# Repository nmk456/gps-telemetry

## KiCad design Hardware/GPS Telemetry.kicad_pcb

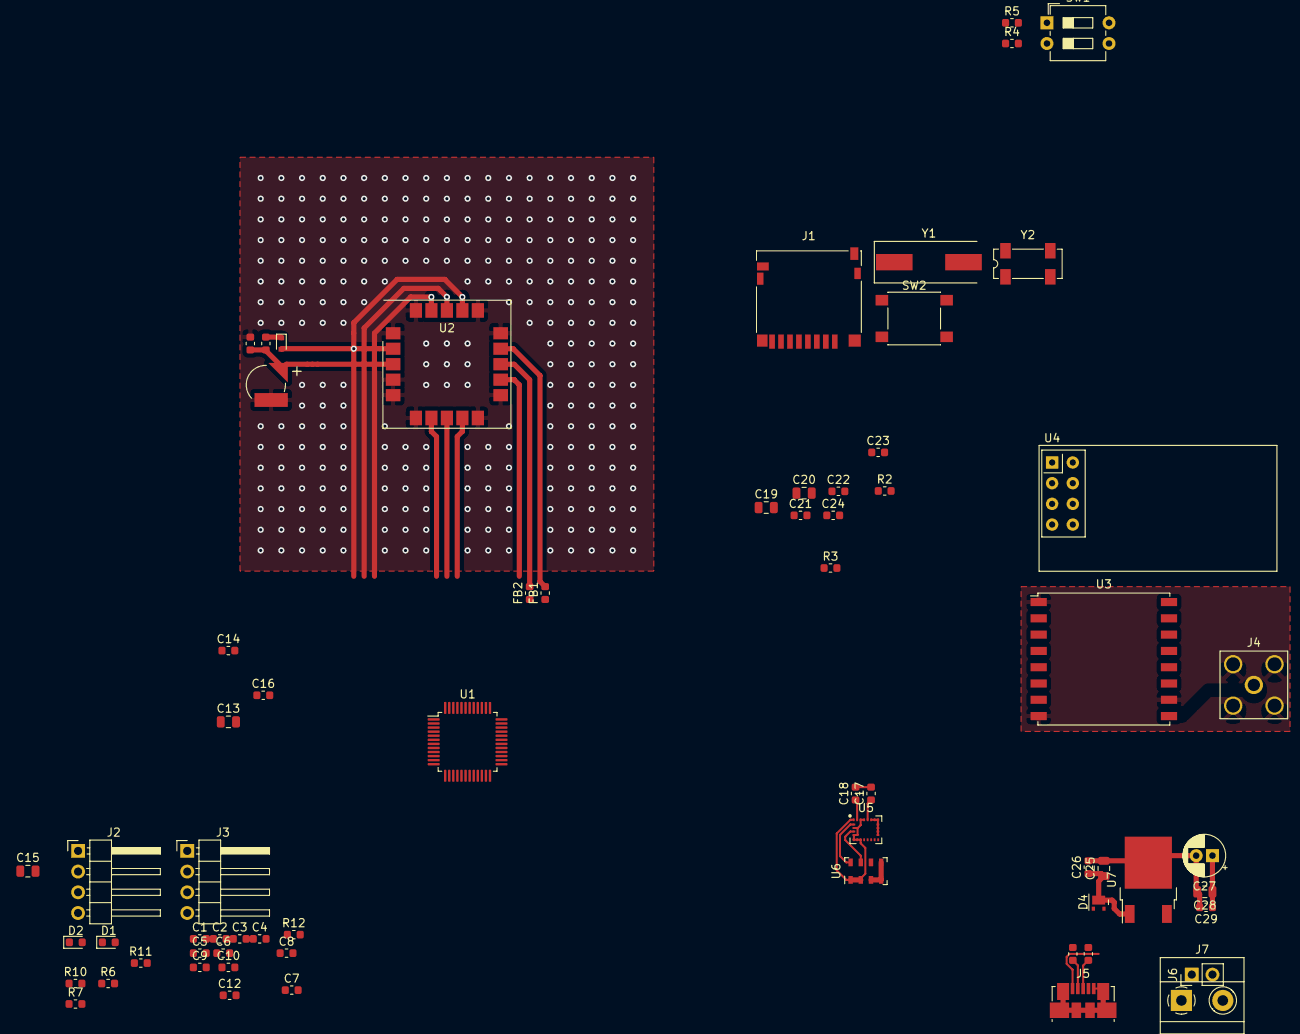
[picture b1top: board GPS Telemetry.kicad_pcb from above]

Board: 2 copper layers, 66 parts (0 on the bottom side), 57 nets.

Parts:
BT1: Battery_Cell; SEIKO_ML414H_IV01E
C1: 4.7u; C_0603_1608Metric
C2, C3, C4, C5, C10, C12, C14, C16, C18, C21, C22, C23, C24, C26, C29: 0.1u; C_0603_1608Metric
C6, C7: 12p; C_0603_1608Metric
C8, C9: 8p; C_0603_1608Metric
C11: 1u; C_0603_1608Metric
C13, C15, C19, C20, C25, C28: 10u; C_0805_2012Metric
C17: 10n; C_0603_1608Metric
C27: 47u; CP_Radial_D5.0mm_P2.00mm
D1, D2: LED; LED_0603_1608Metric
D3: D_Schottky; D_SOD-523
D4: D_Schottky_x2_KCom_AAK; HUSON-3-1EP_2x2mm_P1.3mm_EP1.1x1.6mm
FB1, FB2: R; R_0603_1608Metric
J1: Micro_SD_Card_Det; microSD_HC_Hirose_DM3D-SF
J2: SWD; PinHeader_1x04_P2.54mm_Horizontal
J3: Serial; PinHeader_1x04_P2.54mm_Horizontal
J4: Conn_Coaxial; SMA_Amphenol_132203-12_Horizontal
J5: USB_B_Micro; USB_Micro-B_Molex_47346-0001
J6: Conn_01x02; PinHeader_1x02_P2.54mm_Vertical
J7: Screw_Terminal_01x02; TerminalBlock_Phoenix_MKDS-1,5-2-5.08_1x02_P5.08mm_Horizont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
R1: 1k; R_0603_1608Metric
R2, R3, R4, R5: 4.7k; R_0603_1608Metric
R6, R7: 10k; R_0603_1608Metric
R10: 1.5k; R_0603_1608Metric
R11, R12: 470; R_0603_1608Metric
R13, R14: 22; R_0603_1608Metric
SW1: BOOT; SW_DIP_SPSTx02_Slide_6.7x6.64mm_W7.62mm_P2.54mm_LowProfile
SW2: RST; SW_Push_1P1T_NO_6x6mm_H9.5mm
U1: STM32F103C8Tx; LQFP-48_7x7mm_P0.5mm
U2: ublox_SAM-M8Q
U3: RFM95W; HOPERF_RFM9XW_SMD
U4: NRF24_Breakout; nRF24L01_Breakout
U5: LSM9DS1; LGA-24L_3x3.5mm_P0.43mm
U6: MS5607-02BA; LGA-8_3x5mm_P1.25mm
U7: NCP5501; TO-252-2
Y1: 8M; Crystal_SMD_HC49-SD
Y2: 32.768k; Crystal_SMD_SeikoEpson_MC306-4Pin_8.0x3.2mm

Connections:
+3V3: C1.1, C2.1, C3.1, C4.1, C5.1, C12.1, C13.1, C14.1, C15.1, C16.1, C19.1, C20.1, C21.1, C22.1, C23.1, C24.1, C27.1, C28.1, C29.1, D1.2, D2.2, D3.2, J1.4, J2.4, J3.4, R2.1, R3.1, R10.1, SW1.3, SW1.4, U1.9, U1.24, U1.36, U1.48, U2.2, U2.17, U3.13, U4.2, U5.1, U5.3, U5.5, U5.6, U5.7, U5.8, U5.22, U5.23, U6.1, U6.2, U7.3
+BATT: D4.2, J6.1, J7.1
/IO/POWER/USB_DM: R14.2, U1.32
/IO/POWER/USB_DP: R10.2, R13.1, U1.33
/Microcontroller/A0: U1.10, U3.5
/Microcontroller/A1: U1.11, U4.4
/Microcontroller/A4: U1.14, U4.3
/Microcontroller/A8: U1.29, U4.8
/Microcontroller/A9: U1.30, U5.12
/Microcontroller/A10: U1.31, U5.13
/Microcontroller/A15: U1.38, U3.6
/Microcontroller/B0: U1.18, U2.19
/Microcontroller/B1: U1.19, U2.7
/Microcontroller/B3: U1.39, U2.8
/Microcontroller/B4: U1.40, U2.18
/Microcontroller/B5: U1.41, U5.9
/Microcontroller/B10: U1.21, U5.10
/Microcontroller/B11: U1.22, U5.11
/Microcontroller/BOOT0: R4.2, R7.2, SW1.2
/Microcontroller/BOOT1: R5.2, R6.2, SW1.1
/Microcontroller/CLK_SD: J1.5, U1.26
/Microcontroller/CS_SD: J1.2, U1.25
/Microcontroller/DI_SD: J1.3, U1.28
/Microcontroller/DO_SD: J1.7, U1.27
/Microcontroller/LED: R12.2, U1.2
/Microcontroller/MISO: U1.16, U3.2, U4.7
/Microcontroller/MOSI: U1.17, U3.3, U4.6
/Microcontroller/OSC32_IN: C8.1, U1.3, Y2.2
/Microcontroller/OSC32_OUT: C9.1, U1.4, Y2.1
/Microcontroller/OSCIN: C6.1, U1.5, Y1.2
/Microcontroller/OSCOUT: C7.1, U1.6, Y1.1
/Microcontroller/RX: J3.3, U1.43
/Microcontroller/RX2: FB2.1, U1.13
/Microcontroller/SCK: U1.15, U3.4, U4.5
/Microcontroller/SCL: R3.2, U1.45, U2.12, U5.2, U6.8
/Microcontroller/SDA: R2.2, U1.46, U2.9, U5.4, U6.7
/Microcontroller/SWCLK: J2.2, U1.37
/Microcontroller/SWDIO: J2.3, U1.34
/Microcontroller/TX: J3.2, U1.42
/Sensors/RX_GPS: FB1.1, U1.12
GND: BT1.2, C1.2, C2.2, C3.2, C4.2, C5.2, C6.2, C7.2, C8.2, C9.2, C10.2, C11.2, C12.2, C13.2, C14.2, C15.2, C16.2, C17.2, C18.2, C19.2, C20.2, C21.2, C22.2, C23.2, C24.2, C25.2, C26.2, C27.2, C28.2, C29.2, J1.6, J1.11, J2.1, J3.1, J4.2, J5.5, J5.6, J6.2, J7.2, R4.1, R5.1, R11.2, SW2.1, U1.8, U1.23, U1.35, U1.47, U2.1, U2.4, U2.5, U2.6, U2.10, U2.11, U2.15, U2.16, U2.20, U3.1, U3.8, U3.10, U4.1, U5.14, U5.15, U5.16, U5.17, U5.18, U5.19, U5.20, U6.3, U6.4, U6.5, U7.2
unnamed: BT1.1, C11.1, R1.2, U2.3
unnamed: C10.1, SW2.2, U1.7
unnamed: C17.1, U5.21
unnamed: C18.1, U5.24
unnamed: C25.1, C26.1, D4.3, U7.1
unnamed: D1.1, R11.1
unnamed: D2.1, R12.1
unnamed: D3.1, R1.1
unnamed: FB1.2, U2.14
unnamed: FB2.2, U2.13
unnamed: J4.1, U3.9
unnamed: J5.2, R14.1
unnamed: J5.3, R13.2
unnamed: R6.1, U1.20
unnamed: R7.1, U1.44
VBUS: D4.1, J5.1

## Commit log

2020-04-30 Schematic Probably Done
2020-04-30 Rearranged pins so Serial and I2C are available for external use.
2020-04-30 Had too many resistors on USB data lines
2020-04-30 Ran DRC
2020-04-30 Changed some footprints
